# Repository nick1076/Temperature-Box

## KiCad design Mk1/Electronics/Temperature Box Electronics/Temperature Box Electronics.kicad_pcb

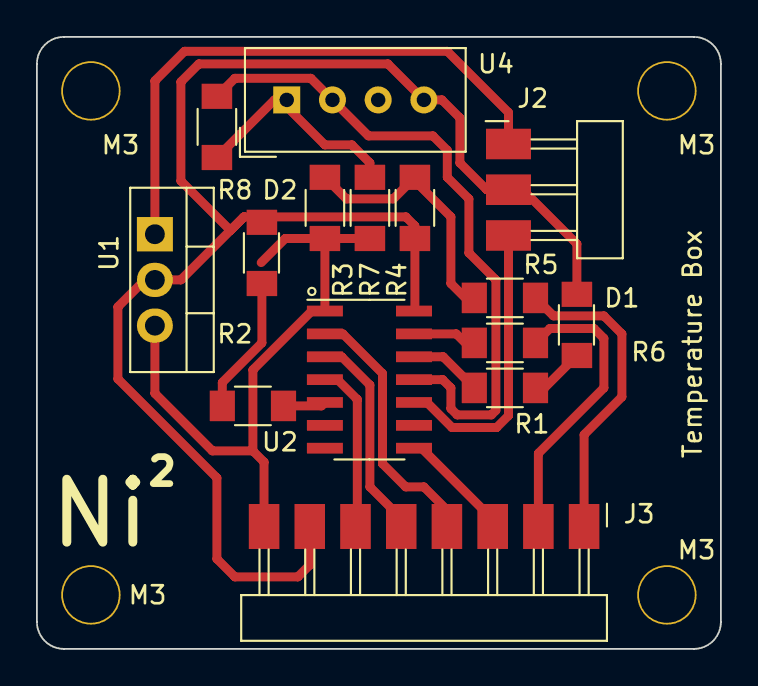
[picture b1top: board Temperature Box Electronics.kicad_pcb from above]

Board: 2 copper layers, 38.0 x 34.0 mm, 19 parts (0 on the bottom side), 18 nets.

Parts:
D1, D2: LED_1206
H1, H2, H3, H4: MountingHole_M3
J2: 1x3 Male Horizontal; PinHeader_1x03_P2.54mm_Horizontal_SMD
J3: 1x8 Male Horizontal; PinHeader_1x08_P2.54mm_Horizontal_SMD
R1, R2, R3: R_1206 330Ω; R_1206
R4: R_1206 640Ω; R_1206
R5, R6, R7: R_1206 0Ω; R_1206
R8: R_1206 4.7kΩ; R_1206
U1: L7805; TO-220-3_Vertical
U2: Microcontroller_ATtiny1614-SSFR; SOIC-14_3.9x8.7mm_P1.27mm
U4: DHT11; Aosong_DHT11_5.5x12.0_P2.54mm

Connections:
unnamed: D1.2 (A), R1.1
unnamed: D1.1 (K), D2.1 (K), J2.2, J3.7, R4.2, U1.2 (GND), U2.14 (GND), U4.4 (GND)
unnamed: D2.2 (A), R2.1
unnamed: J2.1, U1.1 (IN)
unnamed: J2.3, U2.10 (UPDI/PA0)
unnamed: J3.1, R5.2
unnamed: J3.2, R6.2
unnamed: J3.3, U2.8 (SDA/PB1)
unnamed: J3.4, U2.2 (A0/PA4)
unnamed: J3.5, U2.3 (RESET/PA5)
unnamed: J3.6, U2.4 (CS/PA6)
unnamed: J3.8, R3.1, R7.2, U1.3 (OUT), U2.1 (VCC)
unnamed: R3.2, R4.1, R5.1
unnamed: R8.2, U2.11 (DH11/PA1), U4.2 (IO)
unnamed: R1.2, U2.12 (IND1/PA2)
unnamed: R2.2, U2.5 (IND2/PA7)
unnamed: R6.1, U2.13 (SCK/PA3)
unnamed: R7.1, R8.1, U4.1 (VCC)

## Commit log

2024-07-06 Schematic & Design
2024-09-08 Refined code & screen only code
2024-11-22 Mk2 Added
